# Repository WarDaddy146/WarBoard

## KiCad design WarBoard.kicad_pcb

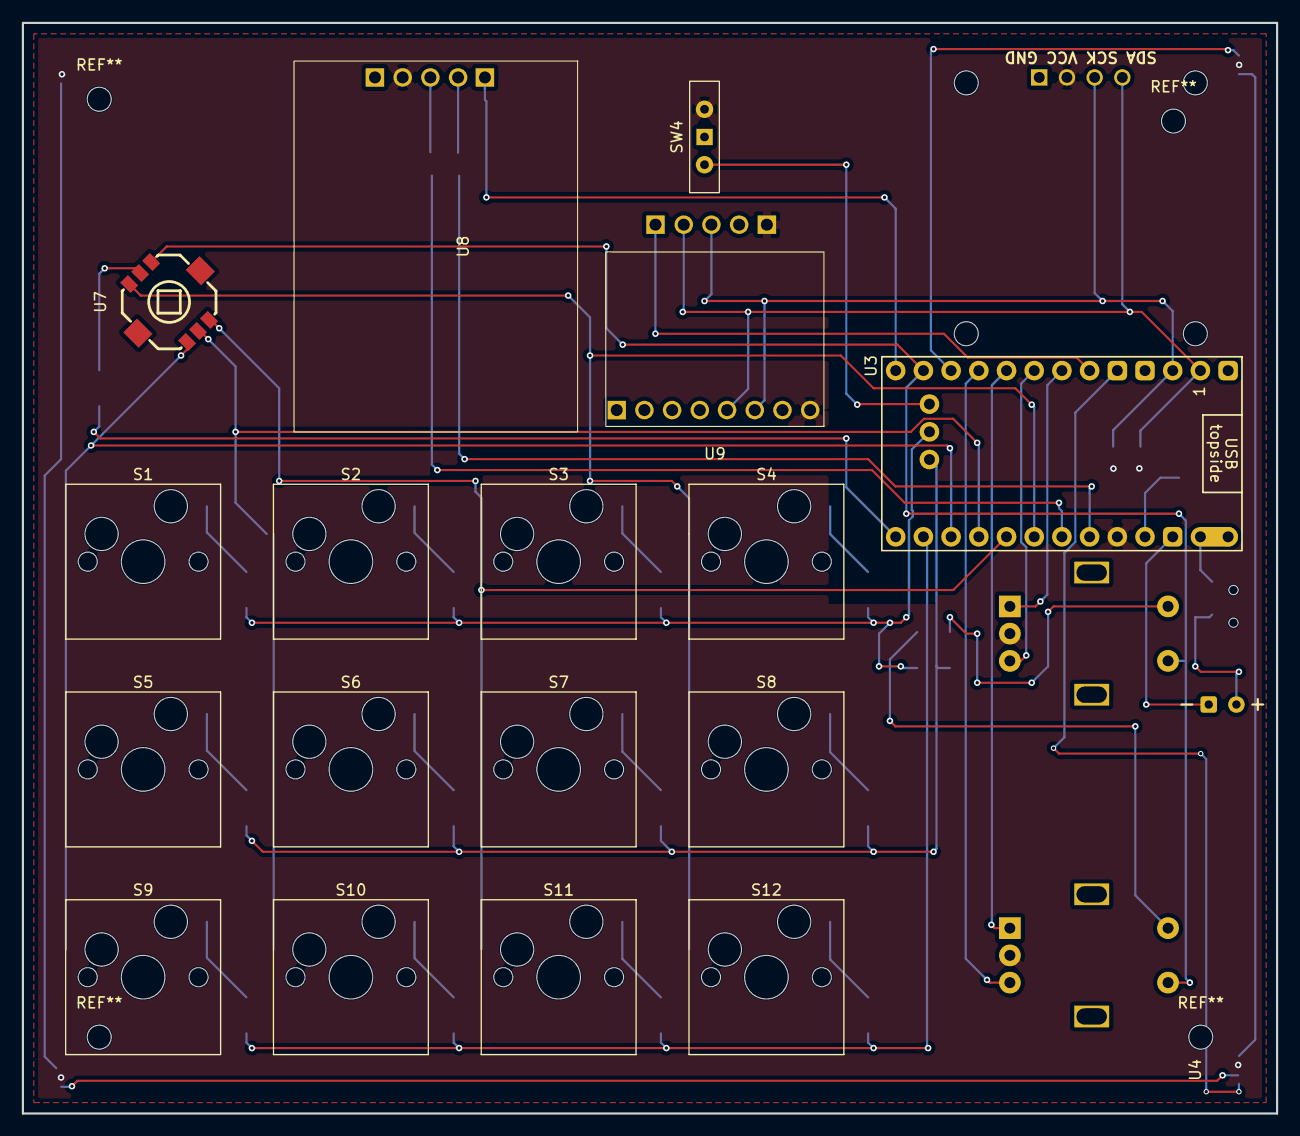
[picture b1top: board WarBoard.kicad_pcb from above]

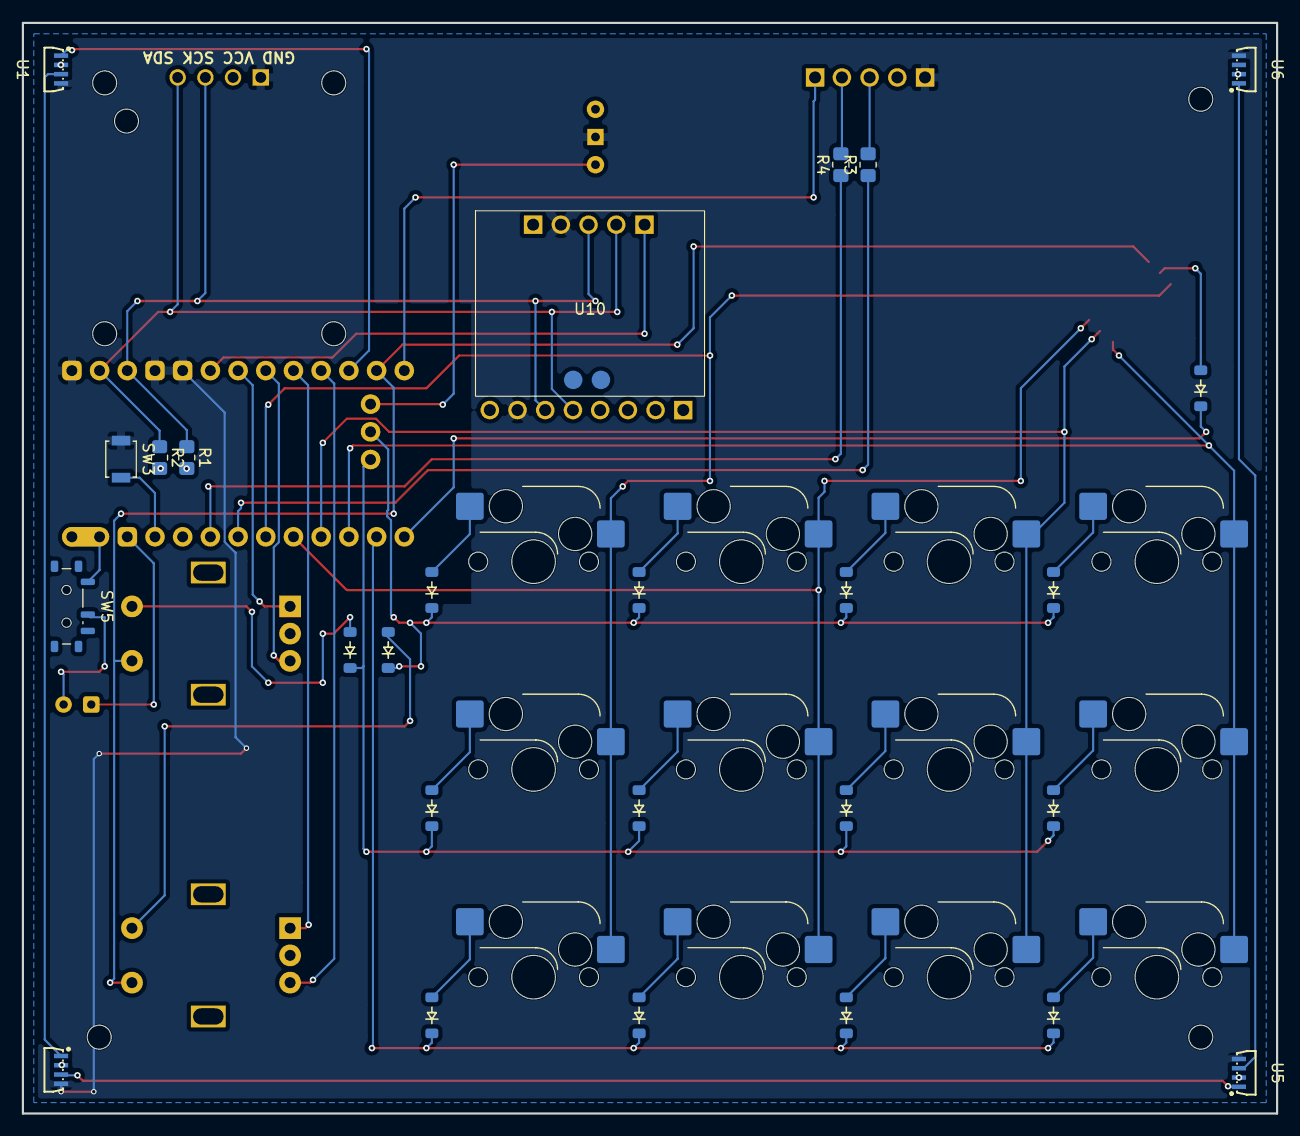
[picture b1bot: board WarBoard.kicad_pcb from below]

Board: 2 copper layers, 115.0 x 100.0 mm, 47 parts (26 on the bottom side), 47 nets.

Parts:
BT1: 3.7 V; Battery
D1, D2, D3, D4, D5, D6, D7, D8, D9, D10, D11, D12, D18, D19, D20: Diode_SOD-123
J1: OLED_128x64
R1, R2: 4.7K; R_0805_2012Metric_Pad1.20x1.40mm_HandSolder
R3, R4: 10k; R_0805_2012Metric_Pad1.20x1.40mm_HandSolder
S1, S2, S3, S4, S5, S6, S7, S8, S9, S10, S11, S12: Hotswap_MX_1.00u
SW1, SW2: RotaryEncoder_Switch; Encoder_EC11_MX
SW3: Reset; SW_SPST_B3U-1000P
SW4: SW_SPDT_321; SW_Slide-03_Wuerth-WS-SLTV_10x2.5x6.4_P2.54mm
SW5: Switch; SW_SPDT_Shouhan_MSK12C02
U1, U4, U5, U6: WS2812B-4020; LED-SMD_WS2812B-4020
U3: SuperMini nRF52840; SuperMini_nRF52840_AH_USBup
U7: SKRHAAE010; SW-SMD_SKRHAAE010
U8: JoyStick; HDR-TH_4P-P2.54-V-M
U9: MPU6050; HDR-TH_4P-P2.54-V-M
U10: DRV2505L; HDR-TH_4P-P2.54-V-M

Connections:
Col_0: S1.1, S5.1, S9.1, U3.22 (P1.11-LF), U7.1
Col_1: S2.1, S6.1, S10.1, U3.21 (P1.13-LF), U7.2
Col_2: S3.1, S7.1, S11.1, U3.20 (P1.15-LF), U7.3
Col_3: S4.1, S8.1, S12.1, U3.19 (P0.02-LF), U7.4
Col_4: SW1.S1, SW2.S1, U3.11 (P1.04-LF), U7.6
GND: J1.1 (GND), SW3.1, SW4.1 (C), U1.4 (VSS), U3.3 (GND), U3.4 (GND), U3.28 (GND), U4.4 (VSS), U5.4 (VSS), U6.4 (VSS), U8.1 (GND), U9.2 (GND), U10.2 (GND)
HAP_TRIG: U3.5 (P0.17), U10.5 (INT)
JS: U3.12 (P1.06-LF), U8.1 (GND)
JX: R3.1, U3.18 (P0.29-LF)
JY: R4.1, U3.17 (P0.31-LF)
LAY: SW4.2 (B), U3.25 (P1.01-LF)
LED: U1.1 (DIN), U3.10 (P0.11)
unnamed: BT1.1 (+), SW5.2
unnamed: BT1.2 (-), U3.14 (GND)
unnamed: D1.2 (A), S1.2
unnamed: D2.2 (A), S2.2
unnamed: D3.2 (A), S3.2
unnamed: D4.2 (A), S4.2
unnamed: D5.2 (A), S5.2
unnamed: D6.2 (A), S6.2
unnamed: D7.2 (A), S7.2
unnamed: D8.2 (A), S8.2
unnamed: D9.2 (A), S9.2
unnamed: D10.2 (A), S10.2
unnamed: D11.2 (A), S11.2
unnamed: D12.2 (A), S12.2
unnamed: D18.2 (A), SW1.S2
unnamed: D19.2 (A), SW2.S2
unnamed: D20.2 (A), U7.5
unnamed: SW5.1, U3.13 (BAT+), U3.29 (BAT+)
unnamed: U1.3 (DOUT), U4.1 (DIN)
unnamed: U4.3 (DOUT), U5.1 (DIN)
unnamed: U5.3 (DOUT), U6.1 (DIN)
unnamed: R3.2, U8.3 (X)
unnamed: R4.2, U8.4 (Y)
RST: SW3.2, U3.15 (RST)
Row_0: D1.1 (K), D2.1 (K), D3.1 (K), D4.1 (K), D18.1 (K), U3.26 (P1.02-LF)
Row_1: D5.1 (K), D6.1 (K), D7.1 (K), D8.1 (K), D19.1 (K), U3.27 (P1.07-LF)
Row_2: D9.1 (K), D10.1 (K), D11.1 (K), D12.1 (K), U3.23 (P0.10-LF)
Row_3: D20.1 (K), U3.24 (P0.09-LF)
SCL: J1.3 (SCL), R1.1, U3.2 (P0.08), U9.3 (SCL), U10.3 (SCL)
SDA: J1.4 (SDA), R2.1, U3.1 (P0.06), U9.4 (SDA), U10.4 (SDA)
SW1_A: SW1.A, U3.8 (P0.24)
SW1_B: SW1.B, U3.9 (P1.00)
SW2_A: SW2.A, U3.6 (P0.20)
SW2_B: SW2.B, U3.7 (P0.22)
VCC: J1.2 (VCC), R1.2, R2.2, SW1.C, SW2.C, SW4.3 (A), U1.2 (VDD), U3.16 (3V3), U4.2 (VDD), U5.2 (VDD), U6.2 (VDD), U8.2 (VCC), U9.1 (VCC), U10.1 (VIN)

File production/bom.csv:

Designator,Footprint,Quantity,Value,LCSC Part #
BT1,Battery,1,3.7 V,
"D1, D10, D11, D12, D18, D19, D2, D20, D3, D4, D5, D6, D7, D8, D9",Diode_SOD-123,15,~,
J1,OLED_128x64,1,OLED_128x64,
"R1, R2",0805,2,4.7K,
"R3, R4",0805,2,10k,
"S1, S10, S11, S12, S2, S3, S4, S5, S6, S7, S8, S9",Hotswap_MX_1.00u,12,~,
"SW1, SW2",Encoder_EC11_MX,2,RotaryEncoder_Switch,
SW3,SW_SPST_B3U-1000P,1,Reset,
SW4,SW_Slide-03_Wuerth-WS-SLTV_10x2.5x6.4_P2.54mm,1,SW_SPDT_321,
SW5,SW_SPDT_Shouhan_MSK12C02,1,Switch,
"U1, U4, U5, U6",LED-SMD_WS2812B-4020,4,WS2812B-4020,C965557
U10,HDR-TH_4P-P2.54-V-M,1,DRV2505L,C2691448
U7,SW-SMD_SKRHAAE010,1,SKRHAAE010,C202423
U8,HDR-TH_4P-P2.54-V-M,1,JoyStick,C2691448
U9,HDR-TH_4P-P2.54-V-M,1,MPU6050,C2691448

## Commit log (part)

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2026-06-29 Initial commit: WarBoard nRF52840 wireless macropad
    KiCad project - 2-layer PCB with 46 components, 392 traces, 57 vias.
    SuperMini nRF52840 BLE MCU, 3x4+encoder matrix, WS2812B LEDs,
    OLED, MPU6050, DRV2605L, joystick, LiPo-powered.
2026-06-30 failsafe: checkpoint before battery wiring and net class fixes
